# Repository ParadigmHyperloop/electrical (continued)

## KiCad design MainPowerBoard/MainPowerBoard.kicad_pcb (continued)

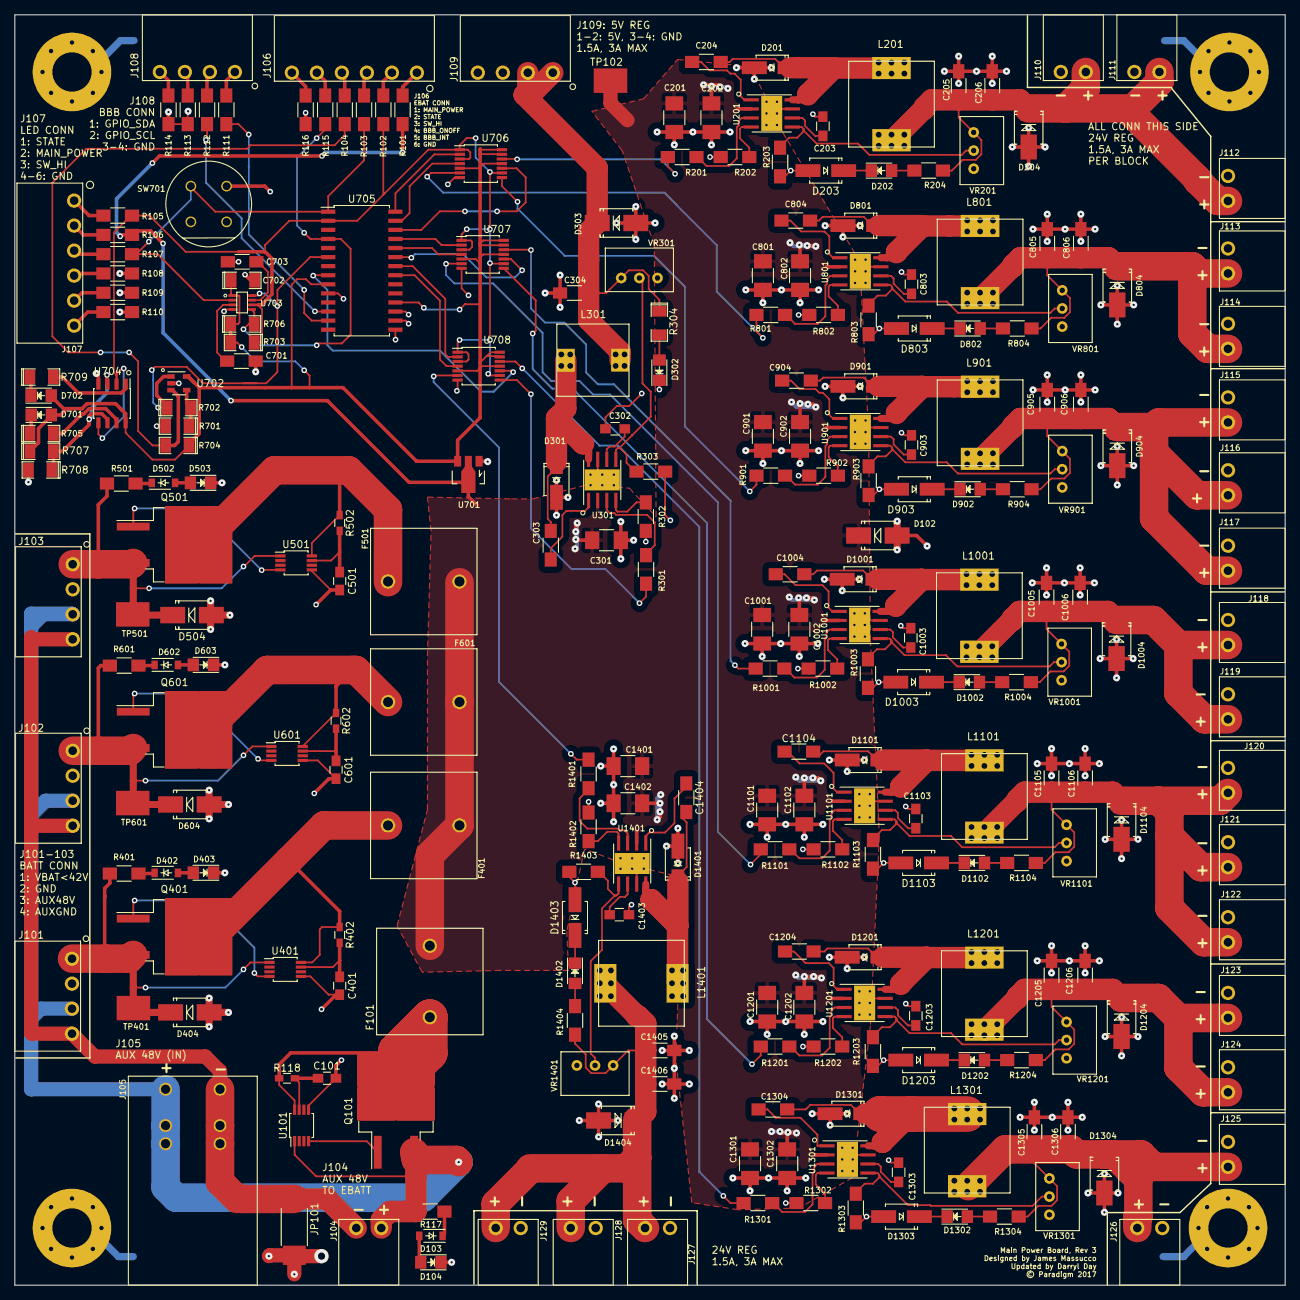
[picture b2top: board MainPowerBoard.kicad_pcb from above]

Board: 2 copper layers, 177.8 x 177.8 mm, 263 parts (0 on the bottom side), 157 nets.

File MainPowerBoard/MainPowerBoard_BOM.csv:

"Id";"Designator";"Package";"Quantity";"Designation";"Supplier and ref";
1;"J107";"CONN_PHOENIX_1844252_6PIN";1;"CONN_01X06";;;
2;"U704";"SOIC-8_3.9x4.9mm_Pitch1.27mm";1;"TLC393";;;
3;"U702";"SOT-23-5";1;"TLV271IDBVR";;;
4;"TP401,TP402,TP403,TP603,TP602,TP601,TP503,TP502,TP501";"TP_SMT_Keystone";9;"Testpoint";;;
5;"F401,F601,F501";"SCHURTER_0031_3804_FUSE";3;"0031.3804";;;
6;"D404,D604,D504";"SMB_Handsoldering";3;"60V";;;
7;"D403,D503,D603,D302,D1402,D1302,D1202,D1102,D1002,D902,D802,D202,D702";"LED_1206";13;"GREEN";;;
8;"R401,R501,R601";"R_1206_HandSoldering";3;"1.5k";;;
9;"C304";"C_1206_HandSoldering";1;"47uF";;;
10;"C302,C1403,C1303,C1203,C1103,C1003,C903,C803,C203";"R_0805_HandSoldering";9;"2.2uF";;;
11;"R303";"R_1206_HandSoldering";1;"12k";;;
12;"D301,D1401,D1301,D1201,D1101,D1001,D901,D801,D201";"SMA_Handsoldering";9;"DIODESCH";;;
13;"R302,R1402,R1302,R1202,R1102,R1002,R902,R802,R202";"R_1206_HandSoldering";9;"47.5k";;;
14;"C301,C1401,C1402,C1302,C1301,C1201,C1202,C1102,C1101,C1002,C1001,C901,C902,C801,C802,C202,C201";"C_1210_HandSoldering";17;"2.2uF";;;
15;"C303,C1404,C1304,C1204,C1104,C1004,C904,C804,C204";"R_1206_HandSoldering";9;"0.1uF";;;
16;"R301,R1401,R1301,R1201,R1101,R1001,R901,R801,R201,R101,R102,R103,R104,R105,R107,R108,R109,R110,R111,R112,R113,R114,R106";"R_1206_HandSoldering";23;"0";;;
17;"VR301";"BOURNS_MULTITURNPOT_3299W";1;"100k";;;
18;"D303";"SMB_Handsoldering";1;"7.5V";;;
19;"D1404,D1304,D1204,D1104,D1004,D904,D804,D204";"SMB_Handsoldering";8;"28V";;;
20;"C1406,C1405,C1305,C1306,C1205,C1206,C1106,C1105,C1006,C1005,C906,C905,C806,C805,C205,C206";"C_1206_HandSoldering";16;"4.7uF";;;
21;"R1403,R1303,R1203,R1103,R1003,R903,R803,R203";"R_1206_HandSoldering";8;"20k";;;
22;"D1403,D1303,D1203,D1103,D1003,D903,D803,D203";"SMA_Handsoldering";8;"18V";;;
23;"L1401,L1301,L1201,L1101,L1001,L901,L801,L201";"47uIND_CDRH127_LDNP-470MC_SUMIDA";8;"47uH";;;
24;"VR1401,VR1301,VR1201,VR1101,VR1001,VR901,VR801,VR201";"BOURNS_MULTITURNPOT_3299W";8;"1M";;;
25;"R1404,R1304,R1204,R1104,R1004,R904,R804,R204";"R_1206_HandSoldering";8;"400";;;
26;"C702";"SMD-1206_Pol";1;"10uF";;;
27;"D701";"LED_1206";1;"RED";;;
28;"R701";"SMD-1206_Pol";1;"100k";;;
29;"R702,R703";"SMD-1206_Pol";2;"500k";;;
30;"R704,R706";"SMD-1206_Pol";2;"10k";;;
31;"R705,R709,R304";"SMD-1206_Pol";3;"300";;;
32;"U701";"Reg_SOT89-3_Diodes_PinNames";1;"UA78L05CPK";;;
33;"J104,J110,J111,J112,J113,J114,J115,J116,J117,J118,J119,J120,J121,J122,J123,J124,J125,J126,J127,J128,J129";"CONN_PHOENIX_1844210_2PIN";21;"CONN_01X02";;;
34;"C701,C703";"C_1206_HandSoldering";2;"C";;;
35;"U703";"LT_LTC2950-1_TSOT-23-8";1;"LTC2950-1";;;
36;"J105";"CONN_PHOENIX_1720466_2PIN";1;"CONN_01X02";;;
37;"R707,R708";"SMD-1206_Pol";2;"1M";;;
38;"L301";"15uIND_SLF10165T-150M3R13PF_BOURNS";1;"15uH";;;
39;"SW701";"PBSW_CW_GPTS203211B";1;"GPTS203211B";;;
40;"J130,J131,J132,J133";"MountingHole_5.5mm_Pad_Via";4;"MOUNTING_HOLE";;;
41;"D401,D601,D501";"DD-PAK_TO263_SingleDiode_ThermalVias";3;"VB30100S-E3/8W";;;
42;"G***";"ParadigmLogo";1;"LOGO";;;
43;"D402,D502,D602";"SOD-123";3;"25V";;;
44;"U201,U301,U801,U901,U1001,U1101,U1201,U1301,U1401";"LMR16030S_8-PowerSOIC_TI";9;"LMR16030S";;;
45;"J101,J102,J103,J106,J108,J109";"CONN_PHOENIX_1844236_4PIN_1";6;"CONN_01X04";;;
46;"G***";"ParadigmLogoRelief";1;"LOGO";;;

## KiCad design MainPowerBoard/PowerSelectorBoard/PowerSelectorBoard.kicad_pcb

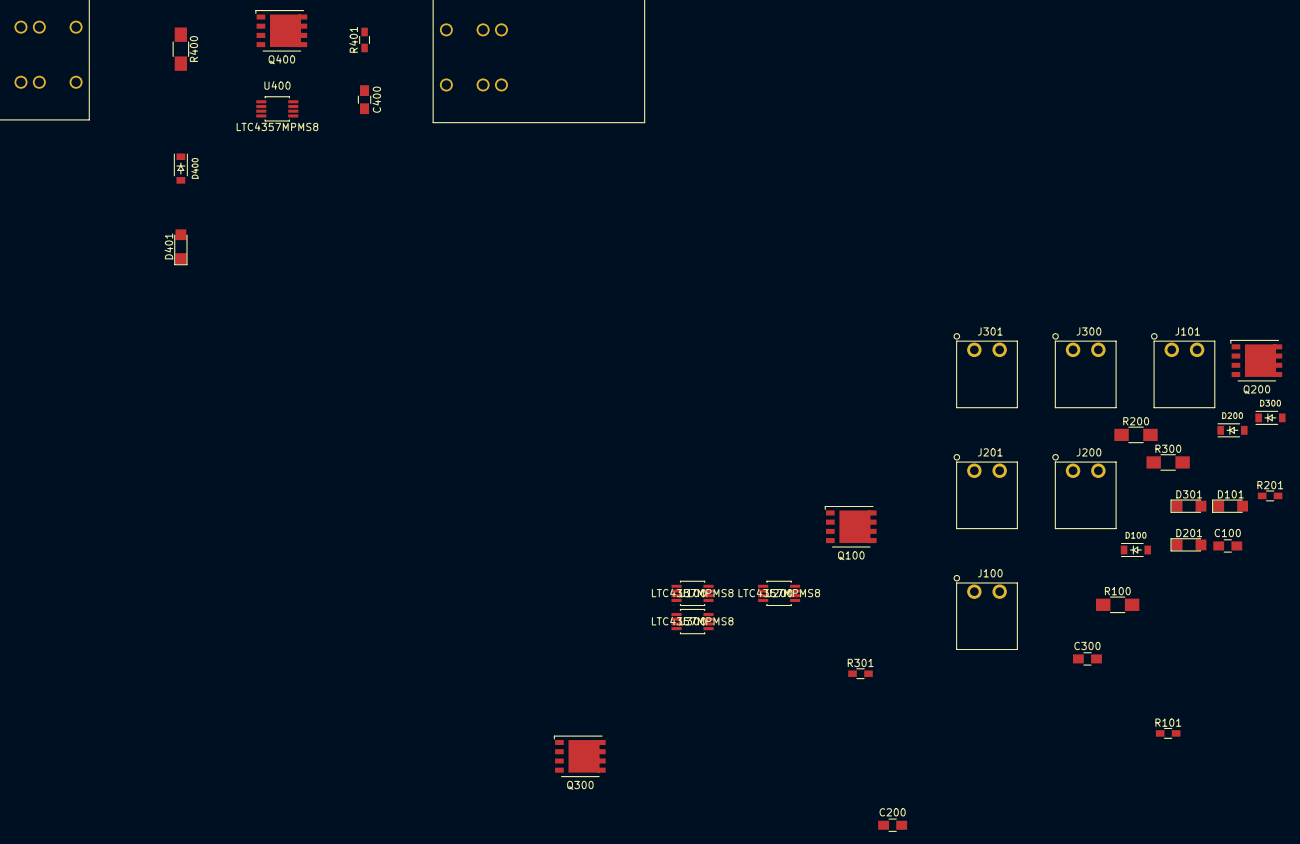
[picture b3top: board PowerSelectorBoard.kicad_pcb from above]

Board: 2 copper layers, 36 parts (0 on the bottom side), 28 nets, no tracks yet.

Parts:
C100, C200, C300, C400: 1uF; C_0805_HandSoldering
D100, D200, D300, D400: 25V; SOD-123
D101, D201, D301, D401: Green; LED_1206
J100, J101, J200, J201, J300, J301: CONN_01X02; CONN_PHOENIX_1844210_2PIN
J400, J401: CONN_01X02; CONN_PHOENIX_1720466_2PIN
Q100, Q200, Q300, Q400: CSD19502Q5B; TDSON-8-1_HandSoldering
R100, R200, R300, R400: 1.5k; R_1206_HandSoldering
R101, R201, R301, R401: 100; R_0603_HandSoldering
U100, U200, U300, U400: LTC4357MPMS8

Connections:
unnamed: C100.1, R101.2, U100.8
unnamed: C100.2, D101.1, J100.1, J101.2, U100.5, U100.7
unnamed: C200.1, R201.2, U200.8
unnamed: C200.2, D201.1, J200.1, J201.2, U200.5, U200.7
unnamed: C300.1, R301.2, U300.8
unnamed: C300.2, D301.1, J300.1, J301.2, U300.5, U300.7
unnamed: C400.1, R401.2, U400.8
unnamed: C400.2, D401.1, J400.1, J401.2, U400.5, U400.7
unnamed: D100.1, R100.2
unnamed: D100.2, D101.2
unnamed: D200.1, R200.2
unnamed: D200.2, D201.2
unnamed: D300.1, R300.2
unnamed: D300.2, D301.2
unnamed: D400.1, R400.2
unnamed: D400.2, D401.2
unnamed: J100.2, Q100.2, R100.1, U100.1
unnamed: J101.1, R101.1
unnamed: J200.2, Q200.2, R200.1, U200.1
unnamed: J201.1, R201.1
unnamed: J300.2, Q300.2, R300.1, U300.1
unnamed: J301.1, R301.1
unnamed: J400.2, Q400.2, R400.1, U400.1
unnamed: J401.1, R401.1
unnamed: Q100.4, U100.4
unnamed: Q200.4, U200.4
unnamed: Q300.4, U300.4
unnamed: Q400.4, U400.4
